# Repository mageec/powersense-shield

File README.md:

powersense-shield
=================

## Power sensing shield for ST Discovery STM32F407VG-based board##

## How to use ##
The boards have been designed using the free Kicad design software, ehich is available at http://www.kicad-pcb.org/display/KICAD/KiCad+EDA+Software+Suite.

Once Kicad is installed, you can open these designs by opening the .pro file in the root directory of the repository.
You will need to add the folder 'kicad' to your library path in the schematic editor and the folder 'kicad/footprints' to your library path in the PCB tool.

#### Acknlowledgments ####

This work is part of the MAGEEC project (http://mageec.org).

Original design by Simon Hollis at University of Bristol (http://www.cs.bris.ac.uk/home/simon/).

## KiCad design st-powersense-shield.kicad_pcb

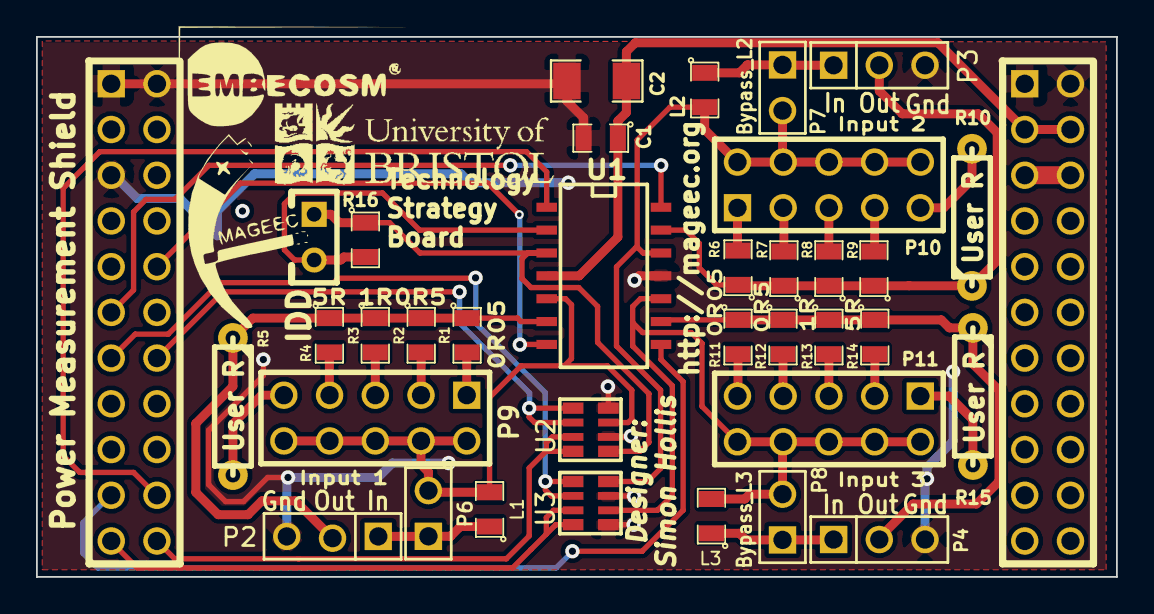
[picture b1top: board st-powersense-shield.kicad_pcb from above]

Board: 2 copper layers, 60.0 x 30.0 mm, 36 parts (0 on the bottom side), 38 nets.

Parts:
C1: 100n; SM0805
C2: 10u; SM1206
L1, L2, L3: 2.2uH; SM0805
P1: Left_Header; pin_array_11x2
P2: Input_1; PIN_ARRAY_3X1
P3: Input_2; PIN_ARRAY_3X1
P4: Input_3; PIN_ARRAY_3X1
P5: IDD; SIL-2
P6: Bypass_L1; PIN_ARRAY_2X1
P7: Bypass_L2; PIN_ARRAY_2X1
P8: Bypass_L3; PIN_ARRAY_2X1
P9: R_select_1; PIN_ARRAY_5x2
P10: R_select_2; PIN_ARRAY_5x2
P11: R_select_3; PIN_ARRAY_5x2
P12: Right_Header; pin_array_11x2
R1, R6, R11: 0R05; SM0805
R2, R7, R12, R16: 0R5; SM0805
R3, R8, R13: 1R; SM0805
R4, R9, R14: 5R; SM0805
R5, R10, R15: UserR; R3-LARGE_PADS
U1: MAX4378; SO14N
U2, U3: 1k; ACAS-0612

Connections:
/3V: P12.5, P12.6
/Amp_1: P1.10, U1.7
/Amp_2: P1.11, U1.14
/Amp_3: P1.19, U1.8
/Amp_uP: P1.20, U1.1
/In_1: L1.1, P2.1, P6.1
/In_2: L2.1, P3.1, P7.1
/In_3: L3.1, P4.1, P8.1
/Out_1: P2.2, R1.1, R2.1, R3.1, R4.1, R5.1, U1.6
/Out_2: P3.2, R6.1, R7.1, R8.1, R9.1, R10.1, U1.13
/Out_3: P4.2, R11.1, R12.1, R13.1, R14.1, R15.1, U1.9
/PA2: P1.14, U2.5, U2.6
/PA3: P1.13, U3.5, U3.6
/PB0: P1.22, U2.7, U2.8
/PB1: P1.21, U3.7, U3.8
/R_In_1: L1.2, P6.2, P9.2, P9.4, P9.6, P9.8, P9.10, U1.5, U2.3
/R_In_2: L2.2, P7.2, P10.2, P10.4, P10.6, P10.8, P10.10, U1.12, U3.4
/R_In_3: L3.2, P8.2, P11.2, P11.4, P11.6, P11.8, P11.10, U1.10, U3.2
/uP_IDD+: P5.1, R16.1, U1.3, U2.1
/uP_IDD-: P5.2, R16.2, U1.2
GND: C1.2, C2.2, P1.1, P1.2, P1.5, P2.3, P3.3, P4.3, P12.1, P12.2, U1.11, U2.2, U2.4, U3.1, U3.3
unnamed: P10.1, R6.2
unnamed: P10.9, R10.2
unnamed: P10.3, R7.2
unnamed: P9.9, R5.2
unnamed: P10.7, R9.2
unnamed: P10.5, R8.2
unnamed: P9.7, R4.2
unnamed: P9.5, R3.2
unnamed: P9.3, R2.2
unnamed: P9.1, R1.2
unnamed: P11.5, R13.2
unnamed: P11.1, R15.2
unnamed: P11.3, R14.2
unnamed: P11.7, R12.2
unnamed: P11.9, R11.2
VAA: C1.1, C2.1, P12.3, P12.4, U1.4
VDD: P1.3, P1.4

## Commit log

2013-05-05 Initial commit of design for STM32F407VG Discovery board ADC shield.`
2013-05-31 Generated and added manufacturing data. Also added logos to repository.
2013-08-06 Updated schematic with originator information.
2013-08-12 Change of license from GPL to CC BY-SA-3.0.
2013-08-12 Update license file name in LICENSE.txt file.
2017-08-19 Add v3 design and v2 and v3 manufacturing data.
